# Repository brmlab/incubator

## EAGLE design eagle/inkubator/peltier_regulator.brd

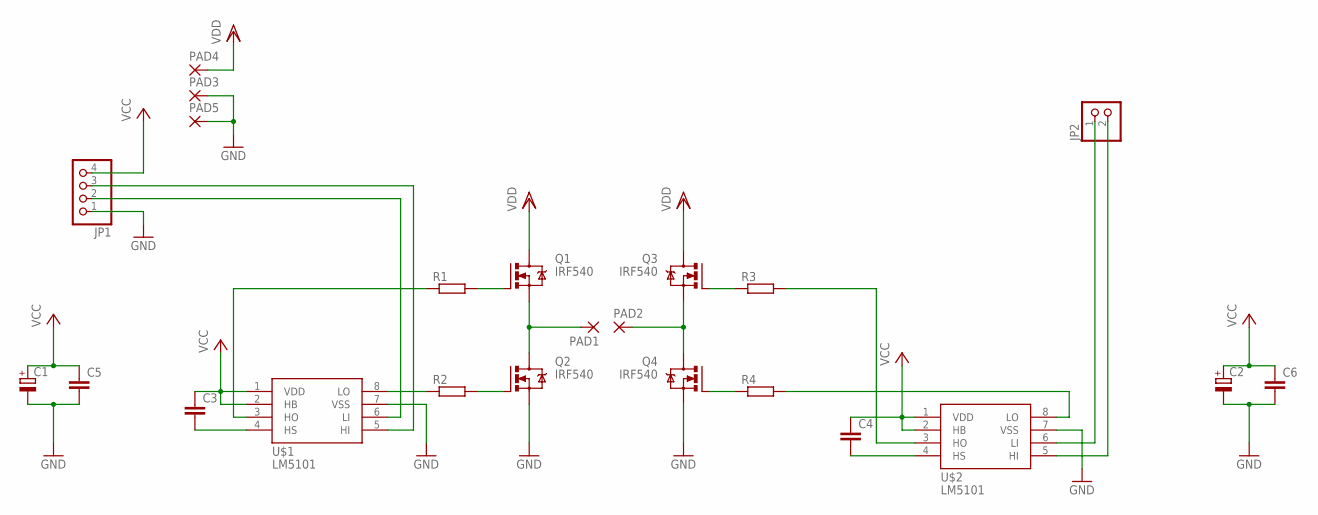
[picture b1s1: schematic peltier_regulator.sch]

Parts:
C1, C2: CPOL-EUD; PANASONIC_D
C3, C4, C5, C6: C-EUC1206; C1206
JP1: PINHD-1X4; 1X04
JP2: PINHD-1X2; 1X02
PAD1, PAD2, PAD3, PAD4, PAD5: 2,54/1,0
Q1, Q2, Q3, Q4: IRF540; TO220BV
R1, R2, R3, R4: R-EU_R1206; R1206
U$1, U$2: LM5101; SOIC8

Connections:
GND: C1.-, C2.-, C5.2, C6.2, JP1.1, PAD3.1, PAD5.1, Q2.S, Q4.S, U$1.7 (VSS), U$2.7 (VSS)
unnamed: C3.2, U$1.4 (HS)
unnamed: Q1.G, R1.2
unnamed: R2.1, U$1.8 (LO)
unnamed: Q2.G, R2.2
unnamed: R1.1, U$1.3 (HO)
unnamed: JP1.2, U$1.6 (LI)
unnamed: JP1.3, U$1.5 (HI)
unnamed: Q4.G, R4.1
unnamed: Q3.G, R3.1
unnamed: C4.2, U$2.4 (HS)
unnamed: R3.2, U$2.3 (HO)
unnamed: R4.2, U$2.8 (LO)
unnamed: JP2.1, U$2.6 (LI)
unnamed: JP2.2, U$2.5 (HI)
unnamed: PAD1.1, Q1.S, Q2.D
unnamed: PAD2.1, Q3.S, Q4.D
VCC: C1.+, C2.+, C3.1, C4.1, C5.1, C6.1, JP1.4, U$1.1 (VDD), U$1.2 (HB), U$2.1 (VDD), U$2.2 (HB)
VDD: PAD4.1, Q1.D, Q3.D

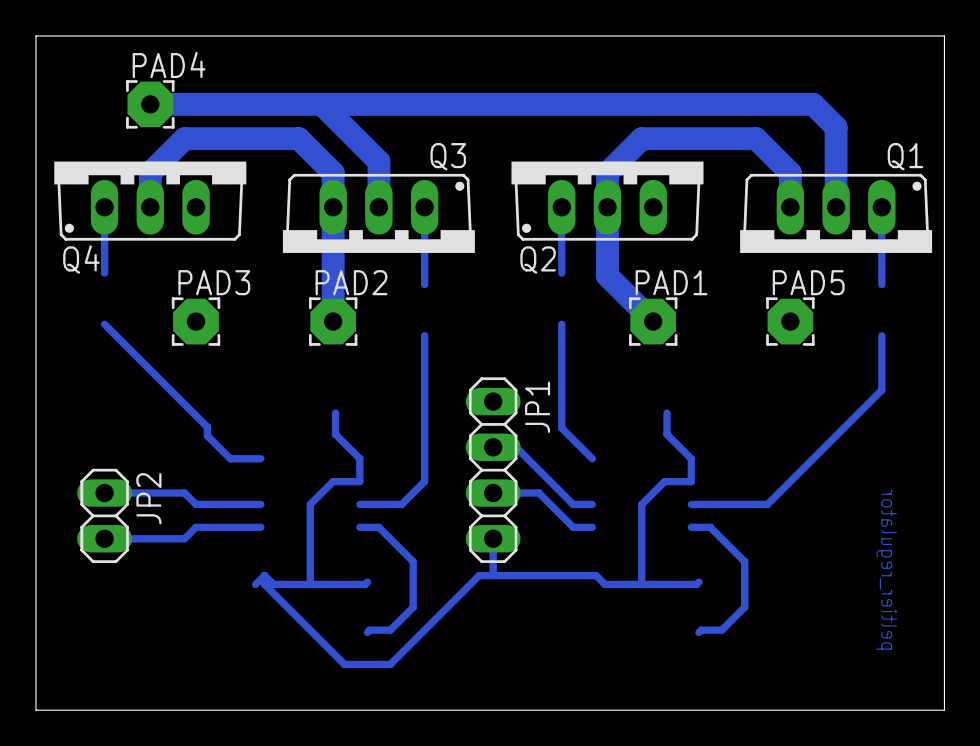
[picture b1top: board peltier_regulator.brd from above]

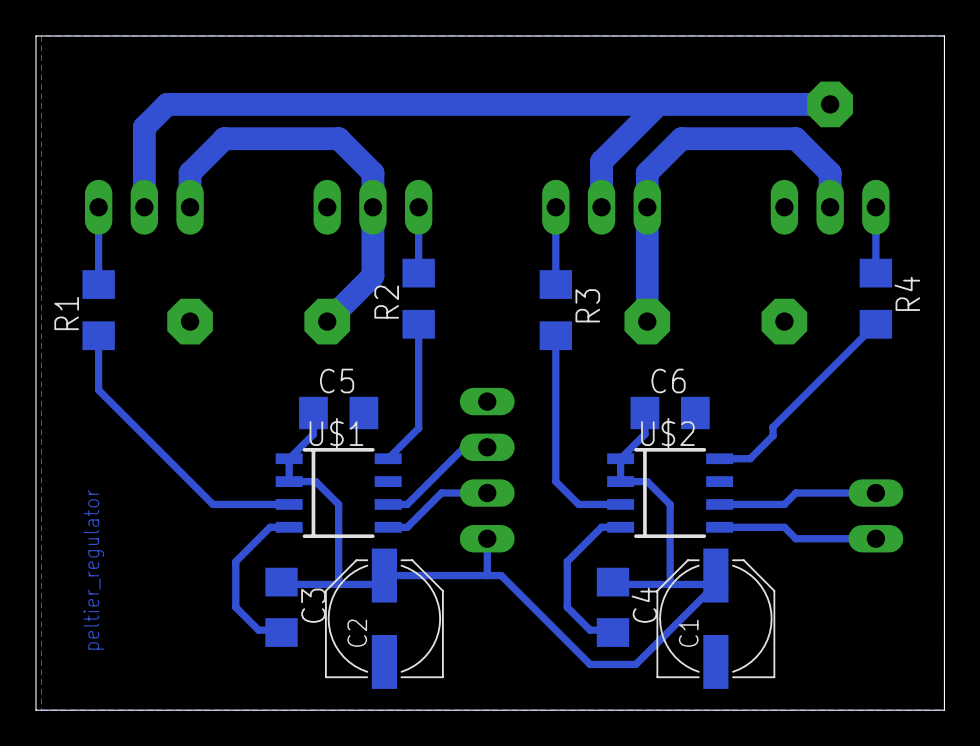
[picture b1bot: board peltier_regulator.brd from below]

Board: 2 copper layers, 50.5 x 37.5 mm, 23 parts (12 on the bottom side), 19 nets.

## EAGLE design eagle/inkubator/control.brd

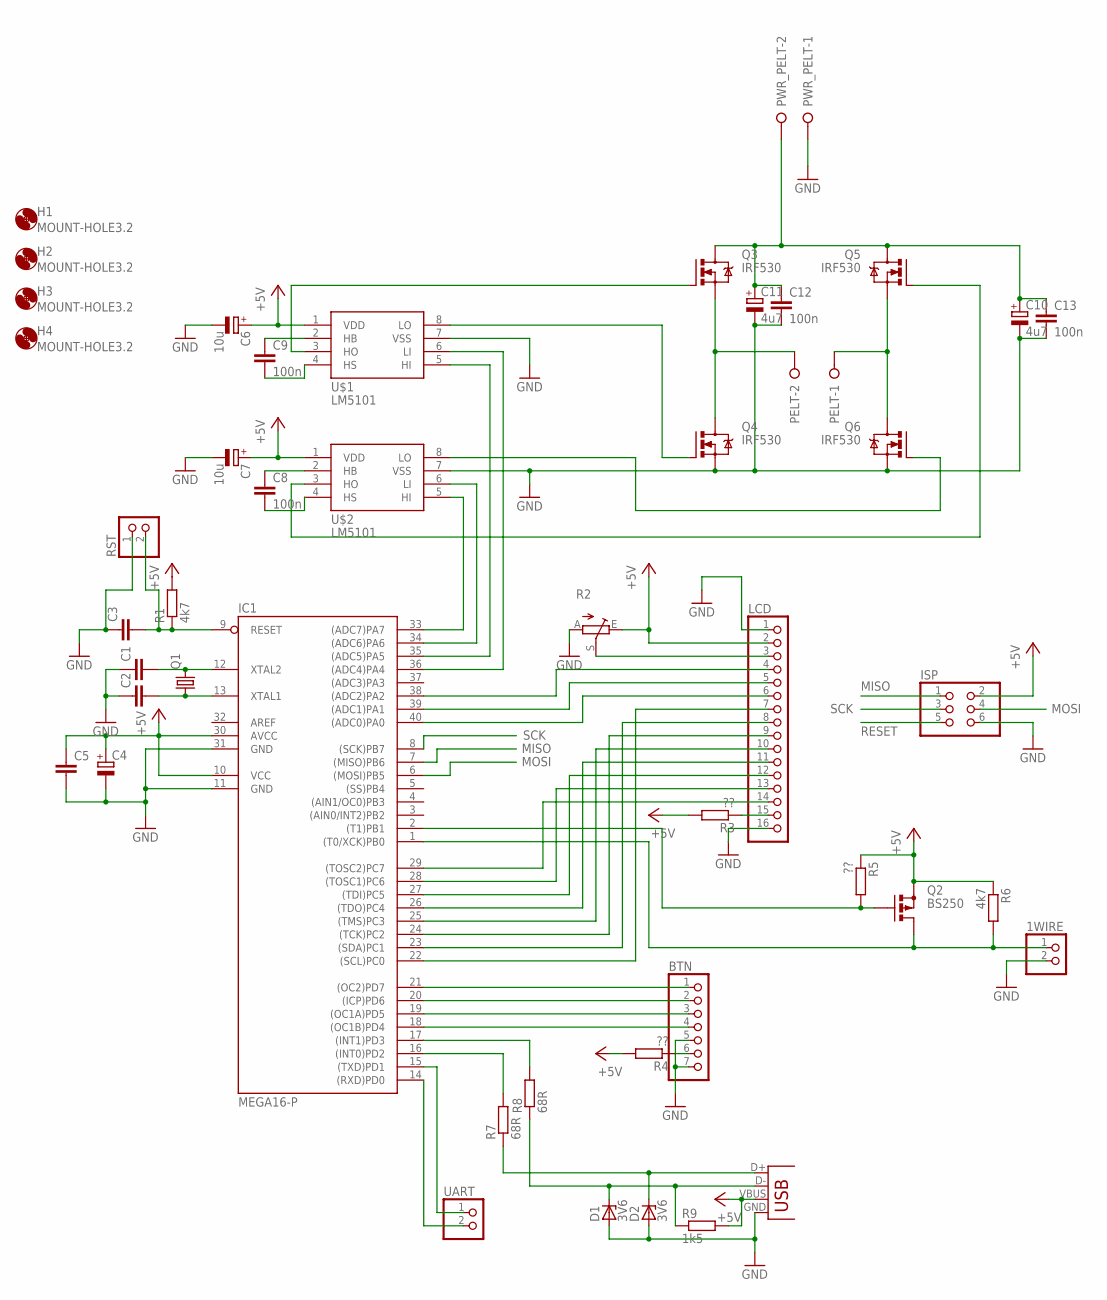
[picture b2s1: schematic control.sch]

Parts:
1WIRE: PINHD-1X2; 1X02
BTN: PINHD-1X7; 1X07
C1, C2: C-EU025-025X050; C025-025X050
C3, C5: C-EU050-024X044; C050-024X044
C4: CPOL-EUE2.5-5; E2,5-5
C6, C7: 10u; E2,5-5
C8, C9, C12, C13: 100n; C025-025X050
C10, C11: 4u7; E5-5
D1, D2: 3V6; ZDIO-7.5
H1, H2, H3, H4: MOUNT-HOLE3.2; 3,2
IC1: MEGA16-P; DIL40
ISP: PINHD-2X3; 2X03
LCD: PINHD-1X16; 1X16
PELT: W237-02P; W237-132
PWR_PELT: W237-02P; W237-132
Q1: CRYSTALHC49U-V; HC49U-V
Q2: BS250; SOT54E
Q3, Q4, Q5, Q6: IRF530; TO220BV
R1, R6: 4k7; 0207/10
R2: TRIM_EU-LI10; LI10
R3, R4, R5: ??; 0207/10
R7, R8: 68R; 0207/10
R9: 1k5; 0207/10
RST: PINHD-1X2; 1X02
U$1, U$2: LM5101; SOIC8
UART: PINHD-1X2; 1X02
X1: USBPTH; USB-B-PTH

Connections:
+5V: C4.+, C5.1, C6.+, C7.+, IC1.10 (VCC), IC1.30 (AVCC), ISP.2, LCD.2, Q2.S, R1.2, R2.E, R3.2, R4.2, R5.1, R6.1, R9.2, U$1.1 (VDD), U$2.1 (VDD), X1.VBUS
GND: 1WIRE.2, BTN.5, BTN.7, C1.1, C2.1, C3.1, C4.-, C5.2, C6.-, C7.-, C10.-, C11.-, C12.2, C13.2, D1.A, D2.A, IC1.11 (GND), IC1.31 (GND), ISP.6, LCD.1, LCD.16, PWR_PELT.1, Q4.S, Q6.S, R2.A, RST.1, U$1.7 (VSS), U$2.7 (VSS), X1.GND
MISO: IC1.7 ((MISO)PB6), ISP.1
MOSI: IC1.6 ((MOSI)PB5), ISP.4
unnamed: C1.2, IC1.12 (XTAL2), Q1.2
unnamed: C2.2, IC1.13 (XTAL1), Q1.1
unnamed: IC1.33 ((ADC7)PA7), U$2.5 (HI)
unnamed: IC1.2 ((T1)PB1), Q2.G, R5.2
unnamed: LCD.3, R2.S
unnamed: LCD.15, R3.1
unnamed: IC1.22 ((SCL)PC0), LCD.7
unnamed: IC1.23 ((SDA)PC1), LCD.8
unnamed: IC1.24 ((TCK)PC2), LCD.9
unnamed: IC1.25 ((TMS)PC3), LCD.10
unnamed: IC1.26 ((TDO)PC4), LCD.11
unnamed: IC1.27 ((TDI)PC5), LCD.12
unnamed: IC1.28 ((TOSC1)PC6), LCD.13
unnamed: IC1.29 ((TOSC2)PC7), LCD.14
unnamed: IC1.40 ((ADC0)PA0), LCD.6
unnamed: IC1.39 ((ADC1)PA1), LCD.5
unnamed: IC1.38 ((ADC2)PA2), LCD.4
unnamed: IC1.16 ((INT0)PD2), R7.2
unnamed: IC1.17 ((INT1)PD3), R8.2
unnamed: BTN.6, R4.1
unnamed: BTN.1, IC1.21 ((OC2)PD7)
unnamed: BTN.2, IC1.20 ((ICP)PD6)
unnamed: BTN.3, IC1.19 ((OC1A)PD5)
unnamed: BTN.4, IC1.18 ((OC1B)PD4)
unnamed: 1WIRE.1, IC1.1 ((T0/XCK)PB0), Q2.D, R6.2
unnamed: IC1.15 ((TXD)PD1), UART.1
unnamed: IC1.14 ((RXD)PD0), UART.2
unnamed: D2.C, R7.1, X1.D+
unnamed: D1.C, R8.1, R9.1, X1.D-
unnamed: IC1.34 ((ADC6)PA6), U$2.6 (LI)
unnamed: IC1.35 ((ADC5)PA5), U$1.5 (HI)
unnamed: IC1.36 ((ADC4)PA4), U$1.6 (LI)
unnamed: C9.1, U$1.2 (HB)
unnamed: C8.1, U$2.2 (HB)
unnamed: C8.2, U$2.4 (HS)
unnamed: C9.2, U$1.4 (HS)
unnamed: PELT.2, Q3.S, Q4.D
unnamed: PELT.1, Q5.S, Q6.D
unnamed: Q3.G, U$1.3 (HO)
unnamed: Q4.G, U$1.8 (LO)
unnamed: Q5.G, U$2.3 (HO)
unnamed: Q6.G, U$2.8 (LO)
unnamed: C10.+, C11.+, C12.1, C13.1, PWR_PELT.2, Q3.D, Q5.D
RESET: C3.2, IC1.9 (RESET), ISP.5, R1.1, RST.2
SCK: IC1.8 ((SCK)PB7), ISP.3

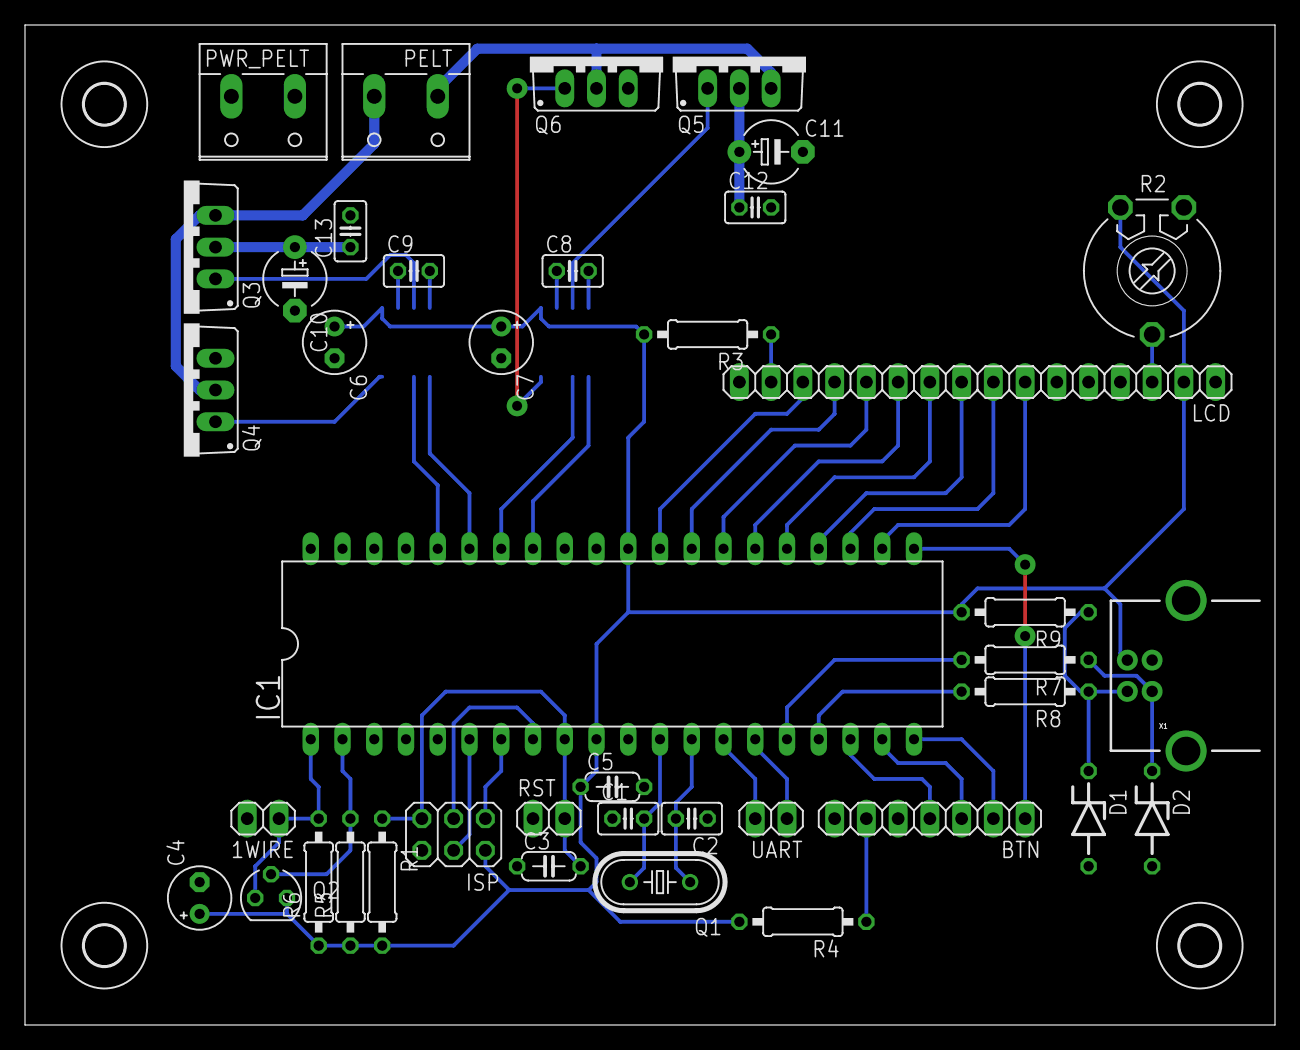
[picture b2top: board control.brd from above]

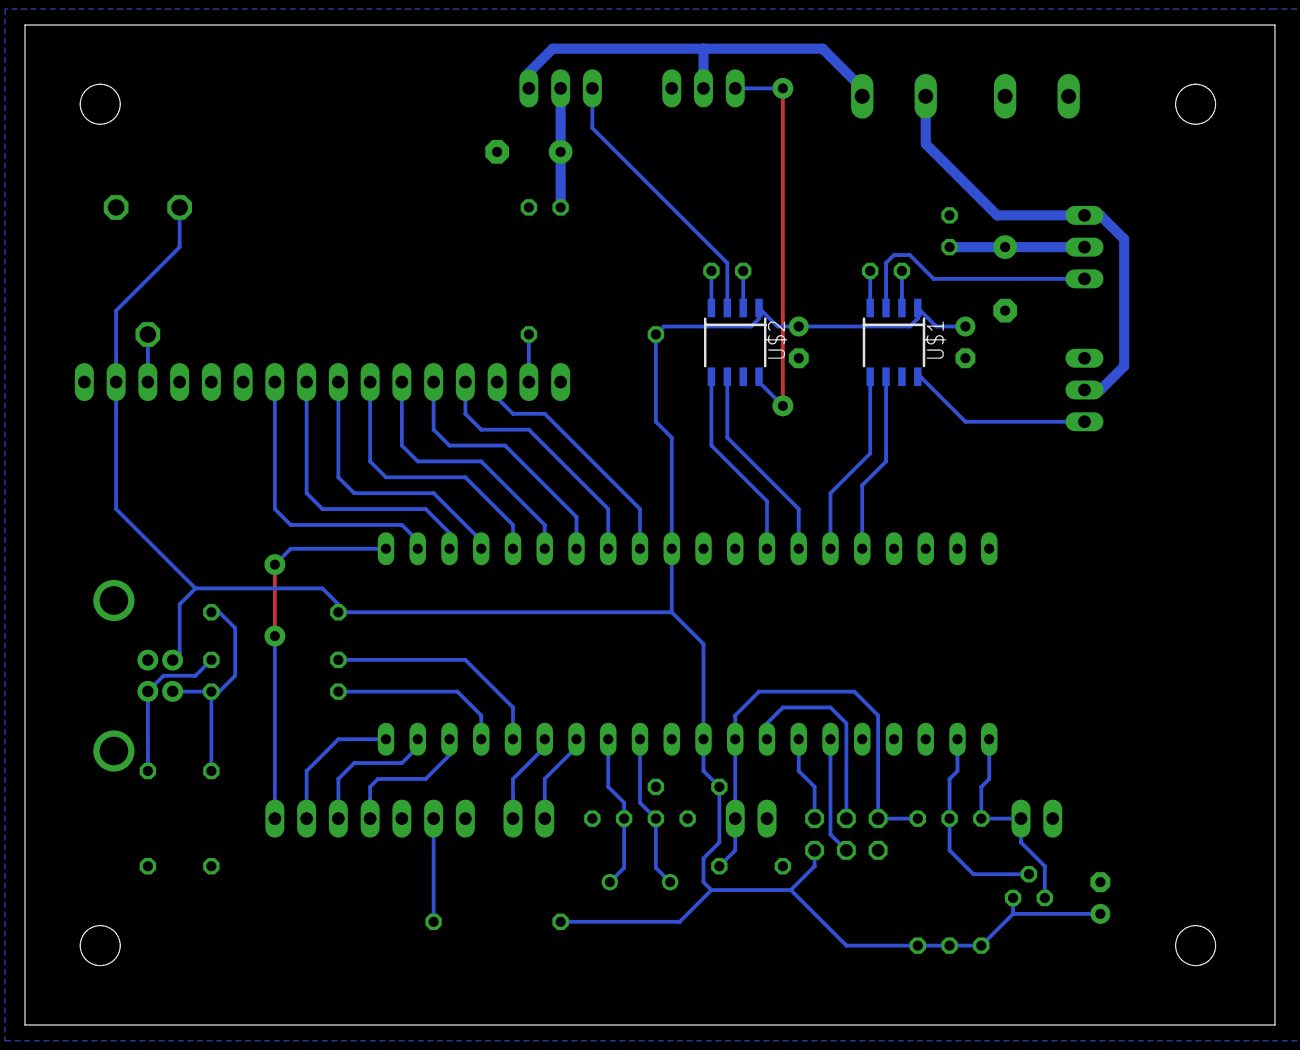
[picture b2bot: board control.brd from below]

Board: 2 copper layers, 100.0 x 80.0 mm, 46 parts (2 on the bottom side), 49 nets.

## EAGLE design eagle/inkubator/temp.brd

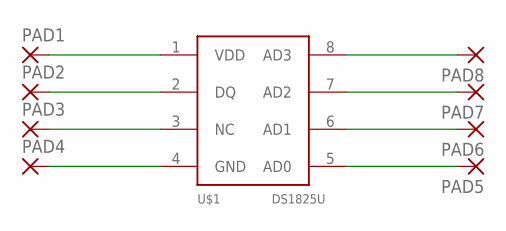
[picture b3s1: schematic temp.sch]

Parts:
PAD1, PAD2, PAD3, PAD4, PAD5, PAD6, PAD7, PAD8: 2,15/1,0
U$1: DS1825U; UMAX8

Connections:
unnamed: PAD1.1, U$1.1 (VDD)
unnamed: PAD2.1, U$1.2 (DQ)
unnamed: PAD3.1, U$1.3 (NC)
unnamed: PAD4.1, U$1.4 (GND)
unnamed: PAD8.1, U$1.8 (AD3)
unnamed: PAD7.1, U$1.7 (AD2)
unnamed: PAD6.1, U$1.6 (AD1)
unnamed: PAD5.1, U$1.5 (AD0)

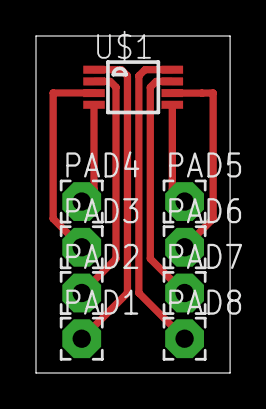
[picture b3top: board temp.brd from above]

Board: 2 copper layers, 10.8 x 18.7 mm, 9 parts (0 on the bottom side), 8 nets.

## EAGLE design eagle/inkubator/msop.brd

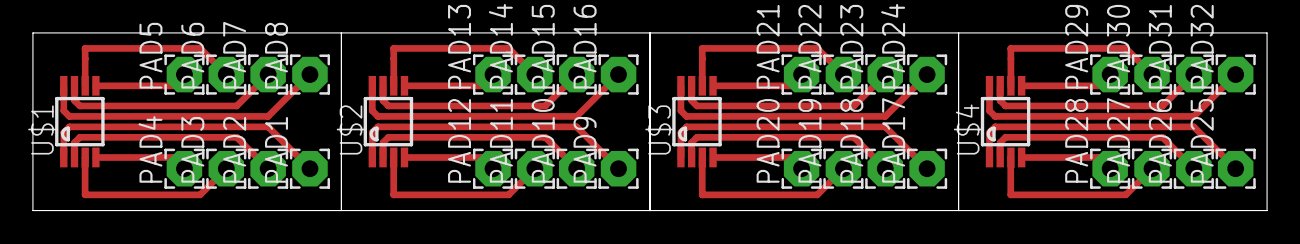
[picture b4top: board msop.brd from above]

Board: 2 copper layers, 74.9 x 10.8 mm, 36 parts (0 on the bottom side), 32 nets.

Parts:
PAD1, PAD2, PAD3, PAD4, PAD5, PAD6, PAD7, PAD8, PAD9, PAD10, PAD11, PAD12, PAD13, PAD14, PAD15, PAD16, PAD17, PAD18, PAD19, PAD20, PAD21, PAD22, PAD23, PAD24, PAD25, PAD26, PAD27, PAD28, PAD29, PAD30, PAD31, PAD32: 2,15/1,0
U$1, U$2, U$3, U$4: DS1825U; UMAX8

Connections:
unnamed: PAD1.1, U$1.1
unnamed: PAD2.1, U$1.2
unnamed: PAD3.1, U$1.3
unnamed: PAD4.1, U$1.4
unnamed: PAD8.1, U$1.8
unnamed: PAD7.1, U$1.7
unnamed: PAD6.1, U$1.6
unnamed: PAD5.1, U$1.5
unnamed: PAD9.1, U$2.1
unnamed: PAD10.1, U$2.2
unnamed: PAD11.1, U$2.3
unnamed: PAD12.1, U$2.4
unnamed: PAD16.1, U$2.8
unnamed: PAD15.1, U$2.7
unnamed: PAD14.1, U$2.6
unnamed: PAD13.1, U$2.5
unnamed: PAD17.1, U$3.1
unnamed: PAD18.1, U$3.2
unnamed: PAD19.1, U$3.3
unnamed: PAD20.1, U$3.4
unnamed: PAD24.1, U$3.8
unnamed: PAD23.1, U$3.7
unnamed: PAD22.1, U$3.6
unnamed: PAD21.1, U$3.5
unnamed: PAD25.1, U$4.1
unnamed: PAD26.1, U$4.2
unnamed: PAD27.1, U$4.3
unnamed: PAD28.1, U$4.4
unnamed: PAD32.1, U$4.8
unnamed: PAD31.1, U$4.7
unnamed: PAD30.1, U$4.6
unnamed: PAD29.1, U$4.5

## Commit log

2012-09-25 todo update
2012-09-25 lm5101 datasheet
2012-10-29 schematic finished, board part 1
2012-10-30 board - almost done
2012-10-31 board v1.0a
2013-09-28 regulator pro peltier
2013-09-28 peltier regulator board

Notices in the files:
parts and their libraries:
SparkFun: Licensing: CC v3.0 Share-Alike You are welcome to use this library for commercial purposes.
